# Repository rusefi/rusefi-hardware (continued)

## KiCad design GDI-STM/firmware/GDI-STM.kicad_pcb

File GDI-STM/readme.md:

GDI based on stm32g4

🔴 zero firmware exists for this hardware 🔴

https://github.com/rusefi/rusefi-hardware/issues/306

https://github.com/rusefi/rusefi-hardware/issues/307

https://rusefi.com/forum/viewtopic.php?f=4&t=1337

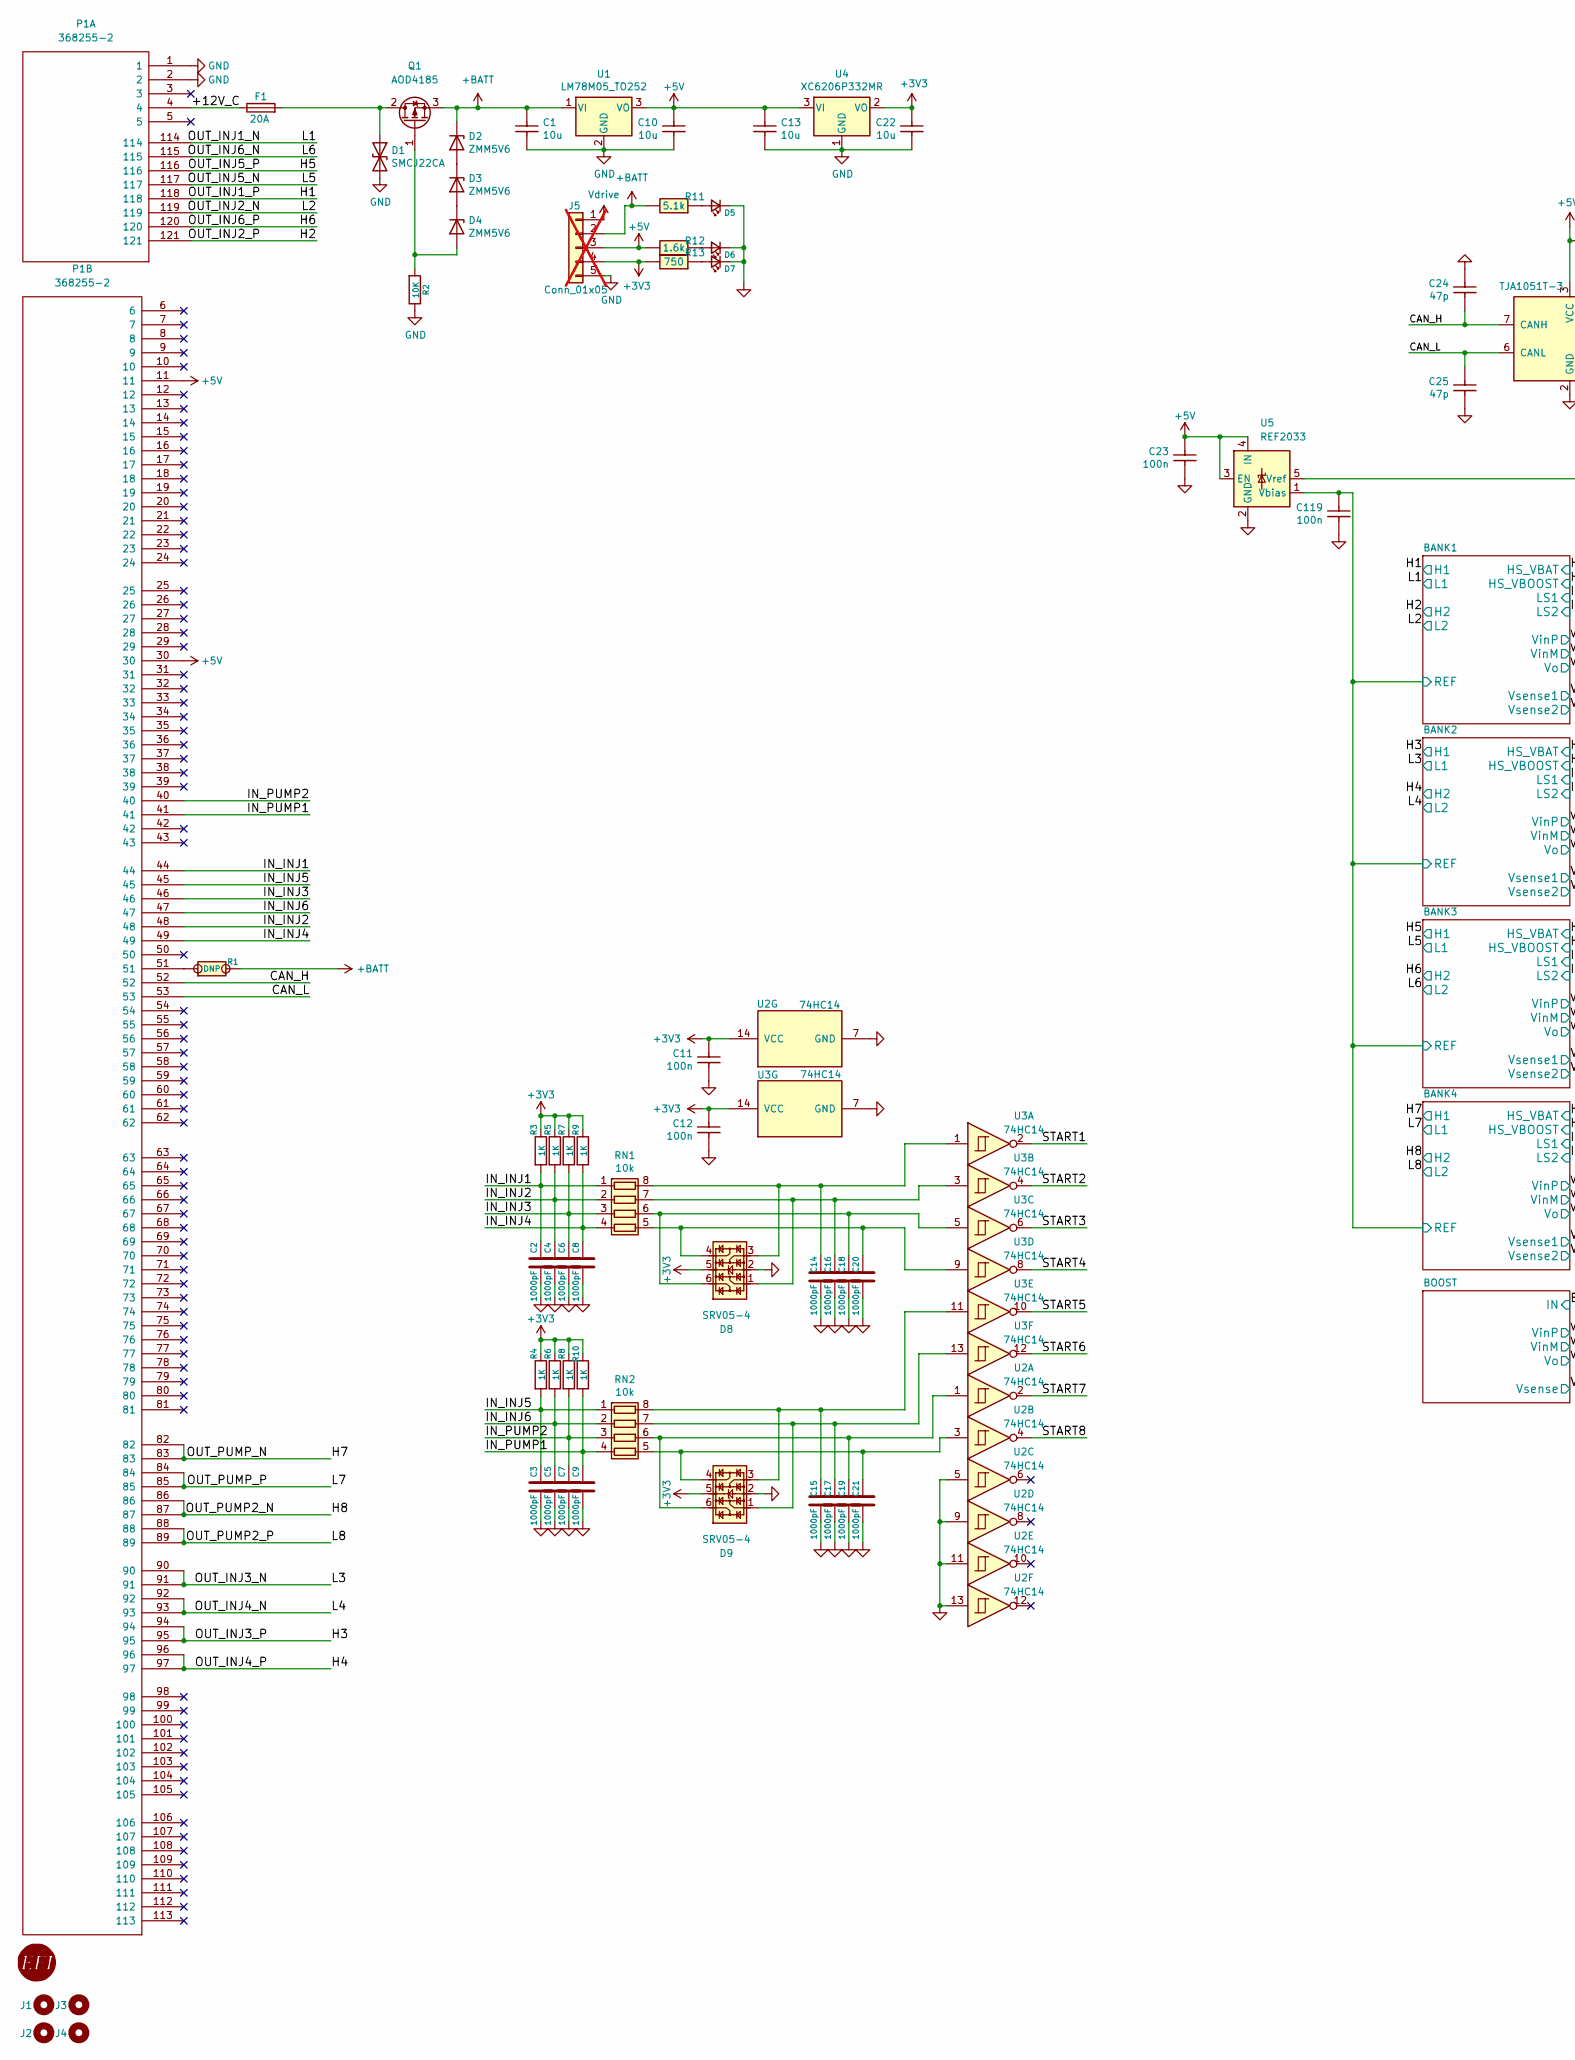
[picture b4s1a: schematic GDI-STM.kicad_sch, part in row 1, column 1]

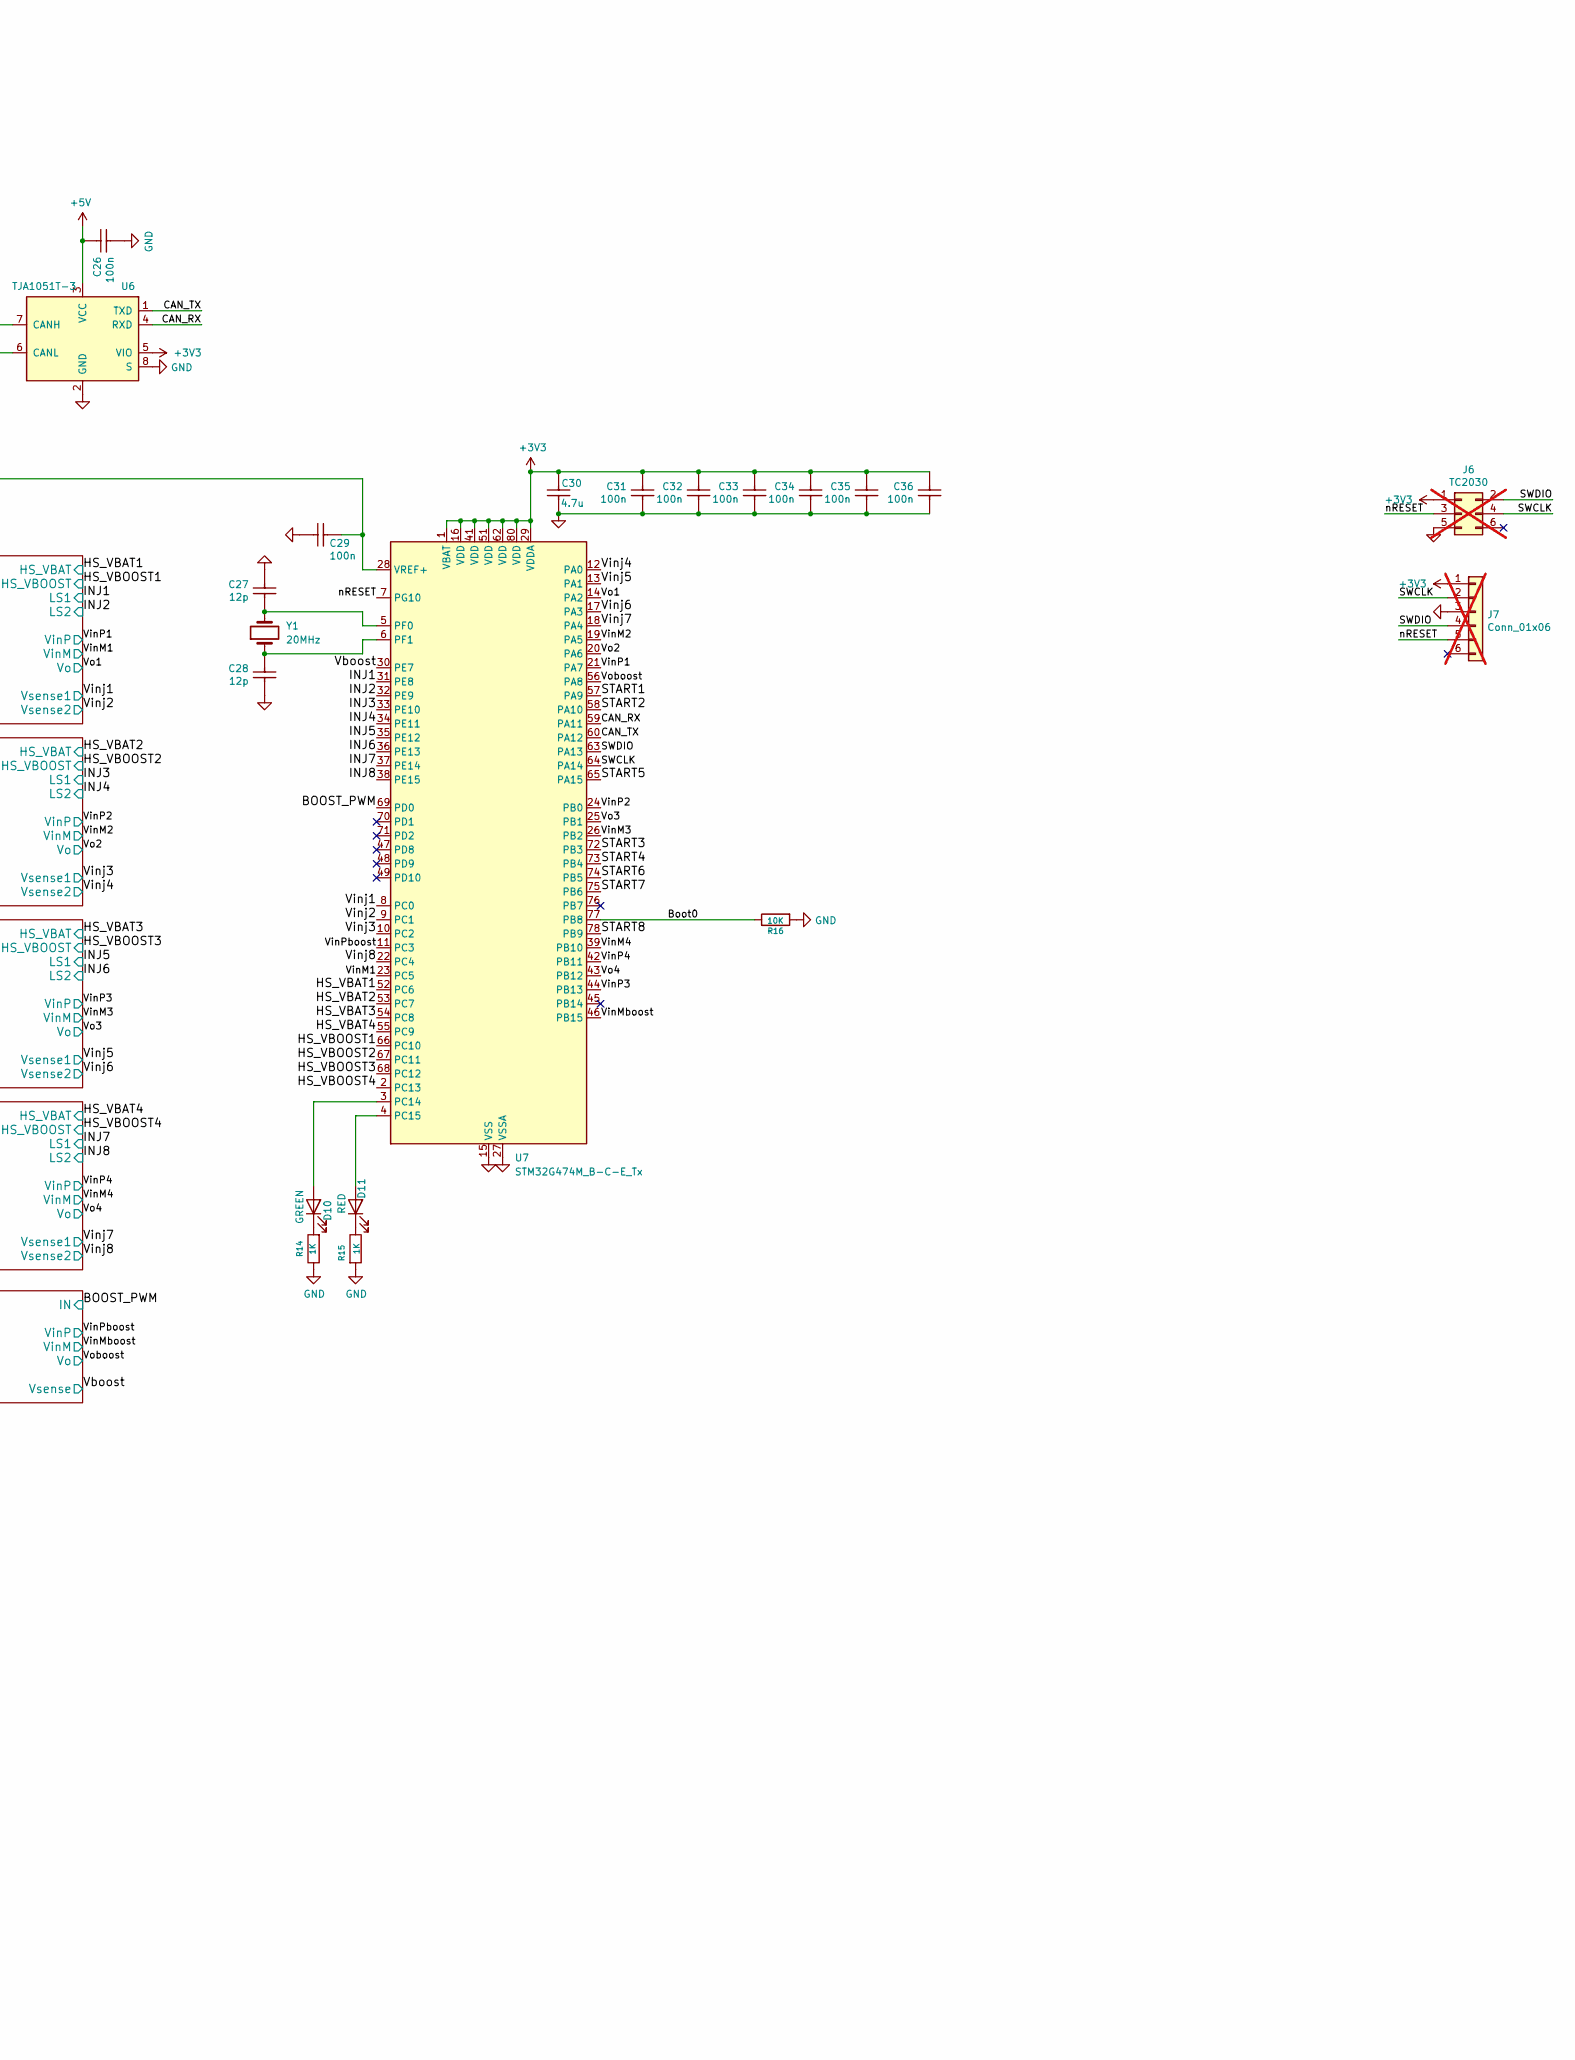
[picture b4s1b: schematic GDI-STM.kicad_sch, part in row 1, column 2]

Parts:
C1, C10, C13, C22: 10u; C_0805_2012Metric; LCSC C15850
C2, C3, C4, C5, C6, C7, C8, C9, C14, C15, C16, C17, C18, C19, C20, C21: 1000pF; C_0603_1608Metric; LCSC C106247
C11, C12, C23, C26, C29, C31, C32, C33, C34, C35, C36, C119: 100n; C0603; LCSC C14663
C24, C25: 47p; C0603; LCSC C1671
C27, C28: 12p; C0603; LCSC C38523
C30: 4.7u; C0603; LCSC C19666
D1: SMCJ22CA; D_SMC; LCSC C151904
D2, D3, D4: ZMM5V6; D_MiniMELF; LCSC C7497481
D5, D6, D7: LED_Small; LED_0805_2012Metric; LCSC C2296
D8, D9: SRV05-4; SOT-23-6; LCSC C85364
D10: GREEN; LED_0603_1608Metric; LCSC C12624
D11: RED; LED_0603_1608Metric; LCSC C2286
F1: 20A; Fuse_1206_3216Metric; LCSC C136357
G1: RUSEFI_LOGO; rusefi_logo
J1, J3: Conn_01x01; MountingHole_3.5mm
J2, J4: Conn_01x01; MountingHole_5.5mm
J5: Conn_01x05; PinHeader_1x05_P2.54mm_Vertical; not fitted
J6: TC2030; Tag-Connect_TC2030-IDC-NL_2x03_P1.27mm_Vertical; not fitted
J7: Conn_01x06; PinHeader_1x06_P2.54mm_Vertical; not fitted
P1: 368255-2; TE_368255-2
Q1: AOD4185; TO-252-2; LCSC C400894
R1: DNP; PAD-0805-PAD
R2, R16: 10K; R_0603_1608Metric; Part # RMCF0603JT10K0; LCSC C25804
R3, R4, R5, R6, R7, R8, R9, R10, R14, R15: 1K; R_0603_1608Metric; LCSC C21190
R11: 5.1k; R0603; LCSC C23186
R12: 1.6k; R0603; LCSC C22847
R13: 750; R0603; LCSC C23241
RN1, RN2: 10k; R_Array_Convex_4x0603; Part # YC164-JR-0710KL; LCSC C29718
U1: LM78M05_TO252; TO-252-2; LCSC C58069
U2, U3: 74HC14; TSSOP-14_4.4x5mm_P0.65mm
U4: XC6206P332MR; SOT-23-3; LCSC C5446
U5: REF2033; SOT-23-5; LCSC C440747
U6: TJA1051T-3; SOIC-8_3.9x4.9mm_P1.27mm; LCSC C38695
U7: STM32G474M_B-C-E_Tx; LQFP-80_12x12mm_P0.5mm; LCSC C5270364
Y1: 20MHz; Crystal_SMD_5032-2Pin_5.0x3.2mm; LCSC C112566

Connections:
+3V3: C11.2, C12.2, C22.2, C30.2, C31.2, C32.2, C33.2, C34.2, C35.2, C36.2, D8.5, D9.5, J5.4, J6.1, J7.1, R3.1, R4.1, R5.1, R6.1, R7.1, R8.1, R9.1, R10.1, R13.2, U2.14 (VCC), U3.14 (VCC), U4.2 (VO), U6.5 (VIO), U7.1 (VBAT), U7.16 (VDD), U7.29 (VDDA), U7.41 (VDD), U7.51 (VDD), U7.62 (VDD), U7.80 (VDD); also elsewhere on the board
+5V: C10.2, C13.2, C23.2, C26.2, J5.3, P1.11, P1.30, R12.2, U1.3 (VO), U4.3 (VI), U5.3 (EN), U5.4 (IN), U6.3 (VCC)
+BATT: C1.2, D2.1 (K), J5.2, Q1.3 (S), R1.2, R11.2, U1.1 (VI); also elsewhere on the board
/+12V_C: F1.1, P1.4
/BANK1/REF: C119.2, U5.1 (Vbias); also elsewhere on the board
/BOOST_PWM: U7.69 (PD0); also elsewhere on the board
/Boot0: R16.1, U7.77 (PB8)
/CAN_H: C24.1, P1.52, U6.7 (CANH)
/CAN_L: C25.2, P1.53, U6.6 (CANL)
/CAN_RX: U6.4 (RXD), U7.59 (PA11)
/CAN_TX: U6.1 (TXD), U7.60 (PA12)
/H1: P1.118, P1.121; also elsewhere on the board
/H3: P1.94, P1.95, P1.96, P1.97; also elsewhere on the board
/H5: P1.116, P1.120; also elsewhere on the board
/H7: P1.82, P1.83, P1.86, P1.87; also elsewhere on the board
/HS_VBAT1: U7.52 (PC6); also elsewhere on the board
/HS_VBAT2: U7.53 (PC7); also elsewhere on the board
/HS_VBAT3: U7.54 (PC8); also elsewhere on the board
/HS_VBAT4: U7.55 (PC9); also elsewhere on the board
/HS_VBOOST1: U7.66 (PC10); also elsewhere on the board
/HS_VBOOST2: U7.67 (PC11); also elsewhere on the board
/HS_VBOOST3: U7.68 (PC12); also elsewhere on the board
/HS_VBOOST4: U7.2 (PC13); also elsewhere on the board
/INJ1: U7.31 (PE8); also elsewhere on the board
/INJ2: U7.32 (PE9); also elsewhere on the board
/INJ3: U7.33 (PE10); also elsewhere on the board
/INJ4: U7.34 (PE11); also elsewhere on the board
/INJ5: U7.35 (PE12); also elsewhere on the board
/INJ6: U7.36 (PE13); also elsewhere on the board
/INJ7: U7.37 (PE14); also elsewhere on the board
/INJ8: U7.38 (PE15); also elsewhere on the board
/IN_INJ1: C2.2, P1.44, R3.2, RN1.1 (R1.1)
/IN_INJ2: C4.2, P1.48, R5.2, RN1.2 (R2.1)
/IN_INJ3: C6.2, P1.46, R7.2, RN1.3 (R3.1)
/IN_INJ4: C8.2, P1.49, R9.2, RN1.4 (R4.1)
/IN_INJ5: C3.2, P1.45, R4.2, RN2.1 (R1.1)
/IN_INJ6: C5.2, P1.47, R6.2, RN2.2 (R2.1)
/IN_PUMP1: C9.2, P1.41, R10.2, RN2.4 (R4.1)
/IN_PUMP2: C7.2, P1.40, R8.2, RN2.3 (R3.1)
/L1: P1.114; also elsewhere on the board
/L2: P1.119; also elsewhere on the board
/L3: P1.90, P1.91; also elsewhere on the board
/L4: P1.92, P1.93; also elsewhere on the board
/L5: P1.117; also elsewhere on the board
/L6: P1.115; also elsewhere on the board
/L7: P1.84, P1.85; also elsewhere on the board
/L8: P1.88, P1.89; also elsewhere on the board
/START1: U3.2, U7.57 (PA9)
/START2: U3.4, U7.58 (PA10)
/START3: U3.6, U7.72 (PB3)
/START4: U3.8, U7.73 (PB4)
/START5: U3.10, U7.65 (PA15)
/START6: U3.12, U7.74 (PB5)
/START7: U2.2, U7.75 (PB6)
/START8: U2.4, U7.78 (PB9)
/SWCLK: J6.4, J7.2, U7.64 (PA14)
/SWDIO: J6.2, J7.4, U7.63 (PA13)
/Vboost: U7.30 (PE7); also elsewhere on the board
/VinM1: U7.23 (PC5); also elsewhere on the board
/VinM2: U7.19 (PA5); also elsewhere on the board
/VinM3: U7.26 (PB2); also elsewhere on the board
/VinM4: U7.39 (PB10); also elsewhere on the board
/VinMboost: U7.46 (PB15); also elsewhere on the board
/VinP1: U7.21 (PA7); also elsewhere on the board
/VinP2: U7.24 (PB0); also elsewhere on the board
/VinP3: U7.44 (PB13); also elsewhere on the board
/VinP4: U7.42 (PB11); also elsewhere on the board
/VinPboost: U7.11 (PC3); also elsewhere on the board
/Vinj1: U7.8 (PC0); also elsewhere on the board
/Vinj2: U7.9 (PC1); also elsewhere on the board
/Vinj3: U7.10 (PC2); also elsewhere on the board
/Vinj4: U7.12 (PA0); also elsewhere on the board
/Vinj5: U7.13 (PA1); also elsewhere on the board
/Vinj6: U7.17 (PA3); also elsewhere on the board
/Vinj7: U7.18 (PA4); also elsewhere on the board
/Vinj8: U7.22 (PC4); also elsewhere on the board
/Vo1: U7.14 (PA2); also elsewhere on the board
/Vo2: U7.20 (PA6); also elsewhere on the board
/Vo3: U7.25 (PB1); also elsewhere on the board
/Vo4: U7.43 (PB12); also elsewhere on the board
/Voboost: U7.56 (PA8); also elsewhere on the board
/nRESET: J6.3, J7.5, U7.7 (PG10)
GND: C1.1, C2.1, C3.1, C4.1, C5.1, C6.1, C7.1, C8.1, C9.1, C10.1, C11.1, C12.1, C13.1, C14.1, C15.1, C16.1, C17.1, C18.1, C19.1, C20.1, C21.1, C22.1, C23.1, C24.2, C25.1, C26.1, C27.2, C28.1, C29.1, C30.1, C31.1, C32.1, C33.1, C34.1, C35.1, C36.1, C119.1, D1.2 (A2), D5.1 (K), D6.1 (K), D7.1 (K), D8.2, D9.2, J5.5, J6.5, J7.3, P1.1, P1.2, R2.1, R14.1, R15.2, R16.2, U1.2 (GND), U2.5, U2.7 (GND), U2.9, U2.11, U2.13, U3.7 (GND), U4.1 (GND), U5.2 (GND), U6.2 (GND), U6.8 (S), U7.15 (VSS), U7.27 (VSSA), U7.40 (VSS), U7.50 (VSS), U7.61 (VSS), U7.79 (VSS); also elsewhere on the board
unnamed: D1.1 (A1), F1.2, Q1.2 (D)
unnamed: D2.2 (A), D3.1 (K)
unnamed: D3.2 (A), D4.1 (K)
unnamed: D4.2 (A), Q1.1 (G), R2.2
unnamed: D5.2 (A), R11.1
unnamed: D6.2 (A), R12.1
unnamed: D7.2 (A), R13.1
unnamed: D10.2 (A), U7.3 (PC14)
unnamed: D10.1 (K), R14.2
unnamed: D11.2 (A), U7.4 (PC15)
unnamed: D11.1 (K), R15.1
unnamed: P1.51, R1.1
unnamed: C14.2, D8.3, RN1.8 (R1.2), U3.1
unnamed: C16.2, D8.1, RN1.7 (R2.2), U3.3
unnamed: C18.2, D8.6, RN1.6 (R3.2), U3.5
unnamed: C20.2, D8.4, RN1.5 (R4.2), U3.9
unnamed: C15.2, D9.3, RN2.8 (R1.2), U3.11
unnamed: C17.2, D9.1, RN2.7 (R2.2), U3.13
unnamed: C19.2, D9.6, RN2.6 (R3.2), U2.1
unnamed: C21.2, D9.4, RN2.5 (R4.2), U2.3
unnamed: C29.2, U5.5 (Vref), U7.28 (VREF+)
unnamed: C27.1, U7.5 (PF0), Y1.2
unnamed: C28.2, U7.6 (PF1), Y1.1
Vdrive: J5.1; also elsewhere on the board

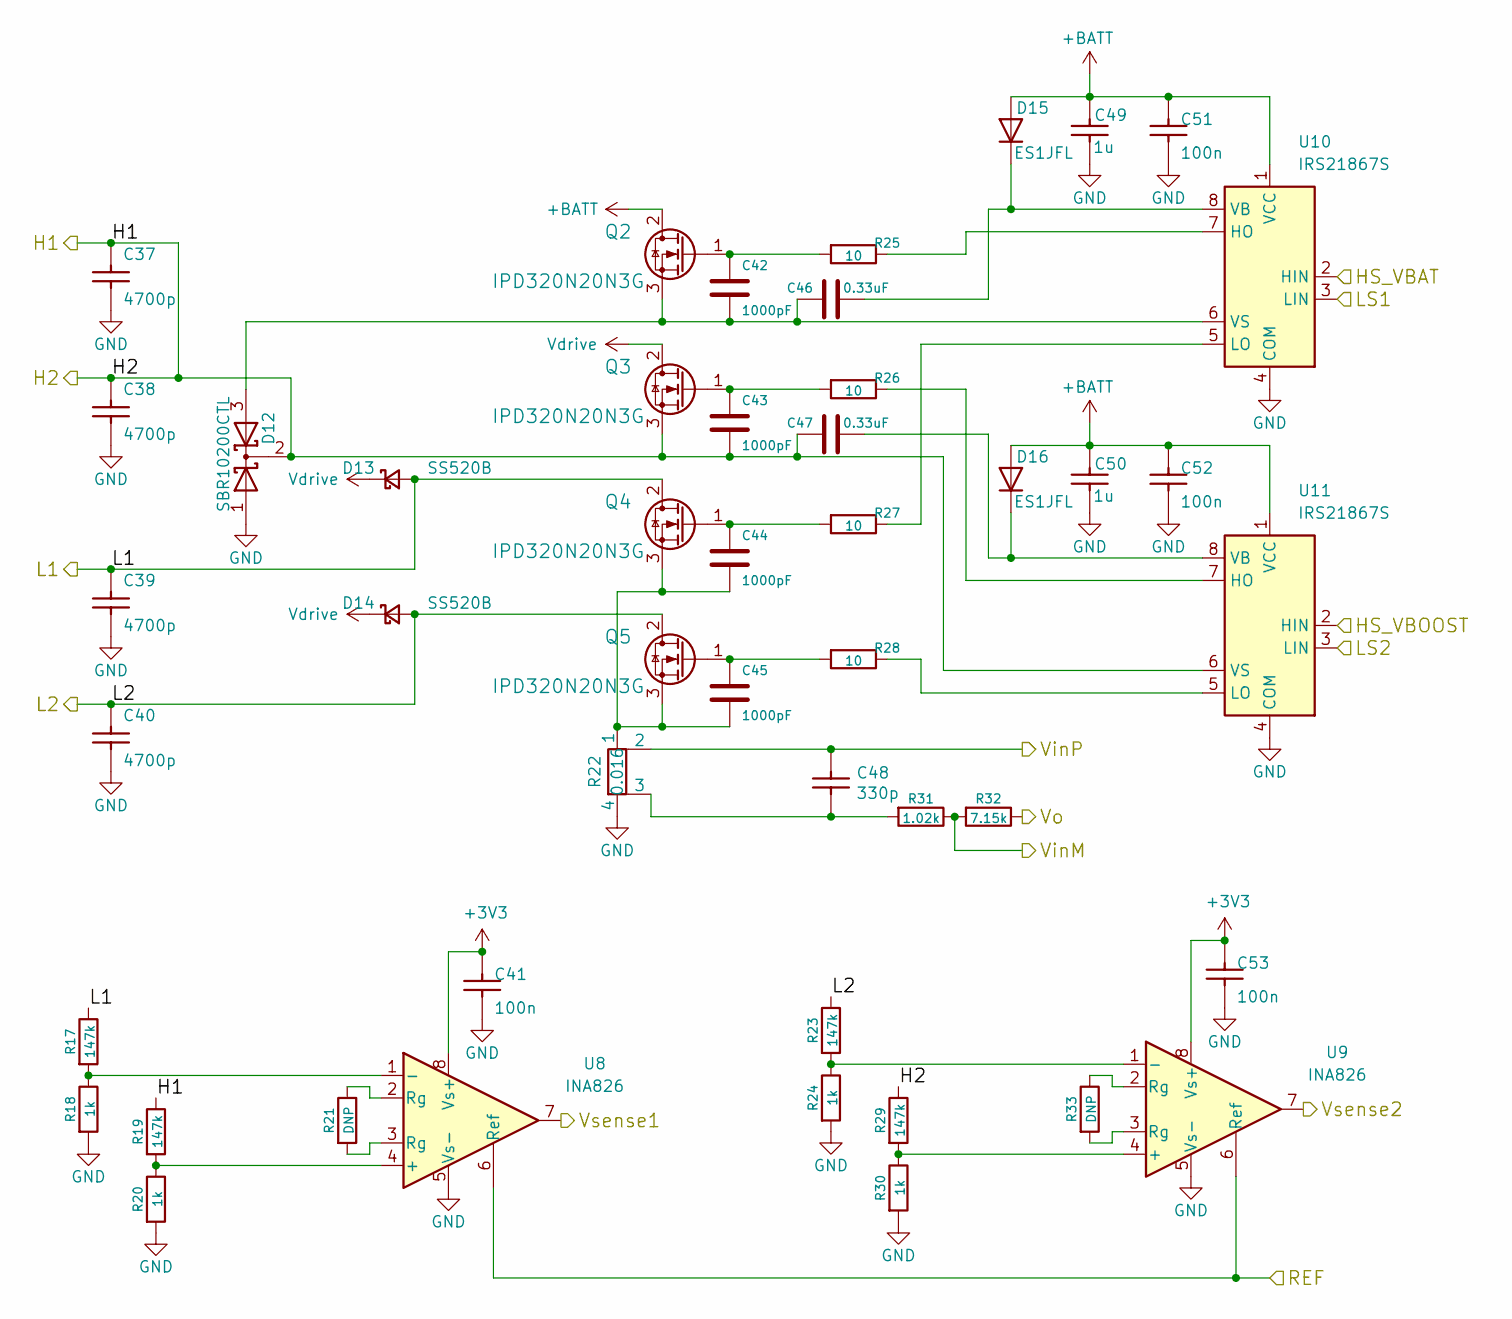
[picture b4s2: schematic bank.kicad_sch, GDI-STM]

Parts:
C37, C38, C39, C40: 4700p; C0603; LCSC C327158
C41, C51, C52, C53: 100n; C0603; LCSC C14663
C42, C43, C44, C45: 1000pF; C_0603_1608Metric; LCSC C106247
C46, C47: 0.33uF; C_0603_1608Metric; LCSC C1615
C48: 330p; C0603; LCSC C576850
C49, C50: 1u; C0603; LCSC C15849
D12: SBR10200CTL; TO-252-2; LCSC C459529
D13, D14: SS520B; D_SMB; LCSC C382826
D15, D16: ES1JFL; D_SOD-123F; LCSC C719809
Q2, Q3, Q4, Q5: IPD320N20N3G; TO-252-2; LCSC C501515
R17, R19, R23, R29: 147k; R_0603_1608Metric; LCSC C22878
R18, R20, R24, R30: 1k; R_0603_1608Metric; LCSC C21190
R21, R33: DNP; R_0603_1608Metric
R22: 0.016; R_Shunt_Vishay_WSK2512_6332Metric_T1.19mm; LCSC C915978
R25, R26, R27, R28: 10; R_0603_1608Metric; LCSC C22859
R31: 1.02k; R_0603_1608Metric; LCSC C22831
R32: 7.15k; R_0603_1608Metric; LCSC C25980
U8, U9: INA826; SOIC-8_3.9x4.9mm_P1.27mm; LCSC C38433
U10, U11: IRS21867S; SOIC-8_3.9x4.9mm_P1.27mm; LCSC C52290

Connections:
+3V3: C41.2, C53.2, U8.8 (Vs+), U9.8 (Vs+); also elsewhere on the board
+BATT: C49.2, C50.2, C51.2, C52.2, D15.2 (A), D16.2 (A), Q2.2 (D), U10.1 (VCC), U11.1 (VCC); also elsewhere on the board
/BANK1/REF: U8.6 (Ref), U9.6 (Ref); also elsewhere on the board
/H1: C37.2, C38.2, C43.1, C47.2, D12.2 (K), Q3.3 (S), R19.1, R29.1, U11.6 (VS); also elsewhere on the board
/HS_VBAT1: U10.2 (HIN); also elsewhere on the board
/HS_VBOOST1: U11.2 (HIN); also elsewhere on the board
/INJ1: U10.3 (LIN); also elsewhere on the board
/INJ2: U11.3 (LIN); also elsewhere on the board
/L1: C39.2, D13.2 (A), Q4.2 (D), R17.1; also elsewhere on the board
/L2: C40.2, D14.2 (A), Q5.2 (D), R23.1; also elsewhere on the board
/VinM1: R31.1, R32.2; also elsewhere on the board
/VinP1: C48.2, R22.2; also elsewhere on the board
/Vinj1: U8.7; also elsewhere on the board
/Vinj2: U9.7; also elsewhere on the board
/Vo1: R32.1; also elsewhere on the board
GND: C37.1, C38.1, C39.1, C40.1, C41.1, C49.1, C50.1, C51.1, C52.1, C53.1, D12.1 (A), R18.2, R20.2, R22.4, R24.2, R30.2, U8.5 (Vs-), U9.5 (Vs-), U10.4 (COM), U11.4 (COM); also elsewhere on the board
unnamed: C48.1, R22.3, R31.2
unnamed: C46.1, D15.1 (K), U10.8 (VB)
unnamed: C47.1, D16.1 (K), U11.8 (VB)
unnamed: C42.2, Q2.1 (G), R25.2
unnamed: C42.1, C46.2, D12.3 (A), Q2.3 (S), U10.6 (VS)
unnamed: C43.2, Q3.1 (G), R26.2
unnamed: C44.2, Q4.1 (G), R27.2
unnamed: C44.1, C45.1, Q4.3 (S), Q5.3 (S), R22.1
unnamed: C45.2, Q5.1 (G), R28.2
unnamed: R21.1, U8.2 (Rg)
unnamed: R21.2, U8.3 (Rg)
unnamed: R33.1, U9.2 (Rg)
unnamed: R33.2, U9.3 (Rg)
unnamed: R19.2, R20.1, U8.4 (+)
unnamed: R17.2, R18.1, U8.1 (-)
unnamed: R29.2, R30.1, U9.4 (+)
unnamed: R23.2, R24.1, U9.1 (-)
unnamed: R25.1, U10.7 (HO)
unnamed: R27.1, U10.5 (LO)
unnamed: R26.1, U11.7 (HO)
unnamed: R28.1, U11.5 (LO)
Vdrive: D13.1 (K), D14.1 (K), Q3.2 (D); also elsewhere on the board

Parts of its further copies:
C54, C55, C56, C57, C71, C72, C73, C74, C88, C89, C90, C91: 4700p; C0603; LCSC C327158
C58, C68, C69, C70, C75, C85, C86, C87, C92, C102, C103, C104: 100n; C0603; LCSC C14663
C59, C60, C61, C62, C76, C77, C78, C79, C93, C94, C95, C96: 1000pF; C_0603_1608Metric; LCSC C106247
C63, C64, C80, C81, C97, C98: 0.33uF; C_0603_1608Metric; LCSC C1615
C65, C82, C99: 330p; C0603; LCSC C576850
C66, C67, C83, C84, C100, C101: 1u; C0603; LCSC C15849
D17, D22, D27: SBR10200CTL; TO-252-2; LCSC C459529
D18, D19, D23, D24, D28, D29: SS520B; D_SMB; LCSC C382826
D20, D21, D25, D26, D30, D31: ES1JFL; D_SOD-123F; LCSC C719809
Q6, Q7, Q8, Q9, Q10, Q11, Q12, Q13, Q14, Q15, Q16, Q17: IPD320N20N3G; TO-252-2; LCSC C501515
R34, R36, R40, R46, R51, R53, R57, R63, R68, R70, R74, R80: 147k; R_0603_1608Metric; LCSC C22878
R35, R37, R41, R47, R52, R54, R58, R64, R69, R71, R75, R81: 1k; R_0603_1608Metric; LCSC C21190
R38, R50, R55, R67, R72, R84: DNP; R_0603_1608Metric
R39, R56, R73: 0.016; R_Shunt_Vishay_WSK2512_6332Metric_T1.19mm; LCSC C915978
R42, R43, R44, R45, R59, R60, R61, R62, R76, R77, R78, R79: 10; R_0603_1608Metric; LCSC C22859
R48, R65, R82: 1.02k; R_0603_1608Metric; LCSC C22831
R49, R66, R83: 7.15k; R_0603_1608Metric; LCSC C25980
U12, U13, U16, U17, U20, U21: INA826; SOIC-8_3.9x4.9mm_P1.27mm; LCSC C38433
U14, U15, U18, U19, U22, U23: IRS21867S; SOIC-8_3.9x4.9mm_P1.27mm; LCSC C52290

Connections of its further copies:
+3V3: C58.2, C70.2, C75.2, C87.2, C92.2, C104.2, U12.8 (Vs+), U13.8 (Vs+), U16.8 (Vs+), U17.8 (Vs+), U20.8 (Vs+), U21.8 (Vs+); also elsewhere on the board
+BATT: C66.2, C67.2, C68.2, C69.2, C83.2, C84.2, C85.2, C86.2, C100.2, C101.2, C102.2, C103.2, D20.2 (A), D21.2 (A), D25.2 (A), D26.2 (A), D30.2 (A), D31.2 (A), Q6.2 (D), Q10.2 (D), Q14.2 (D), U14.1 (VCC), U15.1 (VCC), U18.1 (VCC), U19.1 (VCC), U22.1 (VCC), U23.1 (VCC); also elsewhere on the board
/BANK1/REF: U12.6 (Ref), U13.6 (Ref), U16.6 (Ref), U17.6 (Ref), U20.6 (Ref), U21.6 (Ref); also elsewhere on the board
/H3: C54.2, C55.2, C60.1, C64.2, D17.2 (K), Q7.3 (S), R36.1, R46.1, U15.6 (VS); also elsewhere on the board
/H5: C71.2, C72.2, C77.1, C81.2, D22.2 (K), Q11.3 (S), R53.1, R63.1, U19.6 (VS); also elsewhere on the board
/H7: C88.2, C89.2, C94.1, C98.2, D27.2 (K), Q15.3 (S), R70.1, R80.1, U23.6 (VS); also elsewhere on the board
/HS_VBAT2: U14.2 (HIN); also elsewhere on the board
/HS_VBAT3: U18.2 (HIN); also elsewhere on the board
/HS_VBAT4: U22.2 (HIN); also elsewhere on the board
/HS_VBOOST2: U15.2 (HIN); also elsewhere on the board
/HS_VBOOST3: U19.2 (HIN); also elsewhere on the board
/HS_VBOOST4: U23.2 (HIN); also elsewhere on the board
/INJ3: U14.3 (LIN); also elsewhere on the board
/INJ4: U15.3 (LIN); also elsewhere on the board
/INJ5: U18.3 (LIN); also elsewhere on the board
/INJ6: U19.3 (LIN); also elsewhere on the board
/INJ7: U22.3 (LIN); also elsewhere on the board
/INJ8: U23.3 (LIN); also elsewhere on the board
/L3: C56.2, D18.2 (A), Q8.2 (D), R34.1; also elsewhere on the board
/L4: C57.2, D19.2 (A), Q9.2 (D), R40.1; also elsewhere on the board
/L5: C73.2, D23.2 (A), Q12.2 (D), R51.1; also elsewhere on the board
/L6: C74.2, D24.2 (A), Q13.2 (D), R57.1; also elsewhere on the board
/L7: C90.2, D28.2 (A), Q16.2 (D), R68.1; also elsewhere on the board
/L8: C91.2, D29.2 (A), Q17.2 (D), R74.1; also elsewhere on the board
/VinM2: R48.1, R49.2; also elsewhere on the board
/VinM3: R65.1, R66.2; also elsewhere on the board
/VinM4: R82.1, R83.2; also elsewhere on the board
/VinP2: C65.2, R39.2; also elsewhere on the board
/VinP3: C82.2, R56.2; also elsewhere on the board
/VinP4: C99.2, R73.2; also elsewhere on the board
/Vinj3: U12.7; also elsewhere on the board
/Vinj4: U13.7; also elsewhere on the board
/Vinj5: U16.7; also elsewhere on the board
/Vinj6: U17.7; also elsewhere on the board
/Vinj7: U20.7; also elsewhere on the board
/Vinj8: U21.7; also elsewhere on the board
/Vo2: R49.1; also elsewhere on the board
/Vo3: R66.1; also elsewhere on the board
/Vo4: R83.1; also elsewhere on the board
GND: C54.1, C55.1, C56.1, C57.1, C58.1, C66.1, C67.1, C68.1, C69.1, C70.1, C71.1, C72.1, C73.1, C74.1, C75.1, C83.1, C84.1, C85.1, C86.1, C87.1, C88.1, C89.1, C90.1, C91.1, C92.1, C100.1, C101.1, C102.1, C103.1, C104.1, D17.1 (A), D22.1 (A), D27.1 (A), R35.2, R37.2, R39.4, R41.2, R47.2, R52.2, R54.2, R56.4, R58.2, R64.2, R69.2, R71.2, R73.4, R75.2, R81.2, U12.5 (Vs-), U13.5 (Vs-), U14.4 (COM), U15.4 (COM), U16.5 (Vs-), U17.5 (Vs-), U18.4 (COM), U19.4 (COM), U20.5 (Vs-), U21.5 (Vs-), U22.4 (COM), U23.4 (COM); also elsewhere on the board
unnamed: C65.1, R39.3, R48.2
unnamed: C82.1, R56.3, R65.2
unnamed: C99.1, R73.3, R82.2
unnamed: C63.1, D20.1 (K), U14.8 (VB)
unnamed: C64.1, D21.1 (K), U15.8 (VB)
unnamed: C80.1, D25.1 (K), U18.8 (VB)
unnamed: C81.1, D26.1 (K), U19.8 (VB)
unnamed: C97.1, D30.1 (K), U22.8 (VB)
unnamed: C98.1, D31.1 (K), U23.8 (VB)
unnamed: C59.2, Q6.1 (G), R42.2
unnamed: C59.1, C63.2, D17.3 (A), Q6.3 (S), U14.6 (VS)
unnamed: C60.2, Q7.1 (G), R43.2
unnamed: C61.2, Q8.1 (G), R44.2
unnamed: C61.1, C62.1, Q8.3 (S), Q9.3 (S), R39.1
unnamed: C62.2, Q9.1 (G), R45.2
unnamed: C76.2, Q10.1 (G), R59.2
unnamed: C76.1, C80.2, D22.3 (A), Q10.3 (S), U18.6 (VS)
unnamed: C77.2, Q11.1 (G), R60.2
unnamed: C78.2, Q12.1 (G), R61.2
unnamed: C78.1, C79.1, Q12.3 (S), Q13.3 (S), R56.1
unnamed: C79.2, Q13.1 (G), R62.2
unnamed: C93.2, Q14.1 (G), R76.2
unnamed: C93.1, C97.2, D27.3 (A), Q14.3 (S), U22.6 (VS)
unnamed: C94.2, Q15.1 (G), R77.2
unnamed: C95.2, Q16.1 (G), R78.2
unnamed: C95.1, C96.1, Q16.3 (S), Q17.3 (S), R73.1
unnamed: C96.2, Q17.1 (G), R79.2
unnamed: R38.1, U12.2 (Rg)
unnamed: R38.2, U12.3 (Rg)
unnamed: R50.1, U13.2 (Rg)
unnamed: R50.2, U13.3 (Rg)
unnamed: R55.1, U16.2 (Rg)
unnamed: R55.2, U16.3 (Rg)
unnamed: R67.1, U17.2 (Rg)
unnamed: R67.2, U17.3 (Rg)
unnamed: R72.1, U20.2 (Rg)
unnamed: R72.2, U20.3 (Rg)
unnamed: R84.1, U21.2 (Rg)
unnamed: R84.2, U21.3 (Rg)
unnamed: R36.2, R37.1, U12.4 (+)
unnamed: R34.2, R35.1, U12.1 (-)
unnamed: R46.2, R47.1, U13.4 (+)
unnamed: R40.2, R41.1, U13.1 (-)
unnamed: R42.1, U14.7 (HO)
unnamed: R44.1, U14.5 (LO)
unnamed: R43.1, U15.7 (HO)
unnamed: R45.1, U15.5 (LO)
unnamed: R53.2, R54.1, U16.4 (+)
unnamed: R51.2, R52.1, U16.1 (-)
unnamed: R63.2, R64.1, U17.4 (+)
unnamed: R57.2, R58.1, U17.1 (-)
unnamed: R59.1, U18.7 (HO)
unnamed: R61.1, U18.5 (LO)
unnamed: R60.1, U19.7 (HO)
unnamed: R62.1, U19.5 (LO)
unnamed: R70.2, R71.1, U20.4 (+)
unnamed: R68.2, R69.1, U20.1 (-)
unnamed: R80.2, R81.1, U21.4 (+)
unnamed: R74.2, R75.1, U21.1 (-)
unnamed: R76.1, U22.7 (HO)
unnamed: R78.1, U22.5 (LO)
unnamed: R77.1, U23.7 (HO)
unnamed: R79.1, U23.5 (LO)
Vdrive: D18.1 (K), D19.1 (K), D23.1 (K), D24.1 (K), D28.1 (K), D29.1 (K), Q7.2 (D), Q11.2 (D), Q15.2 (D); also elsewhere on the board

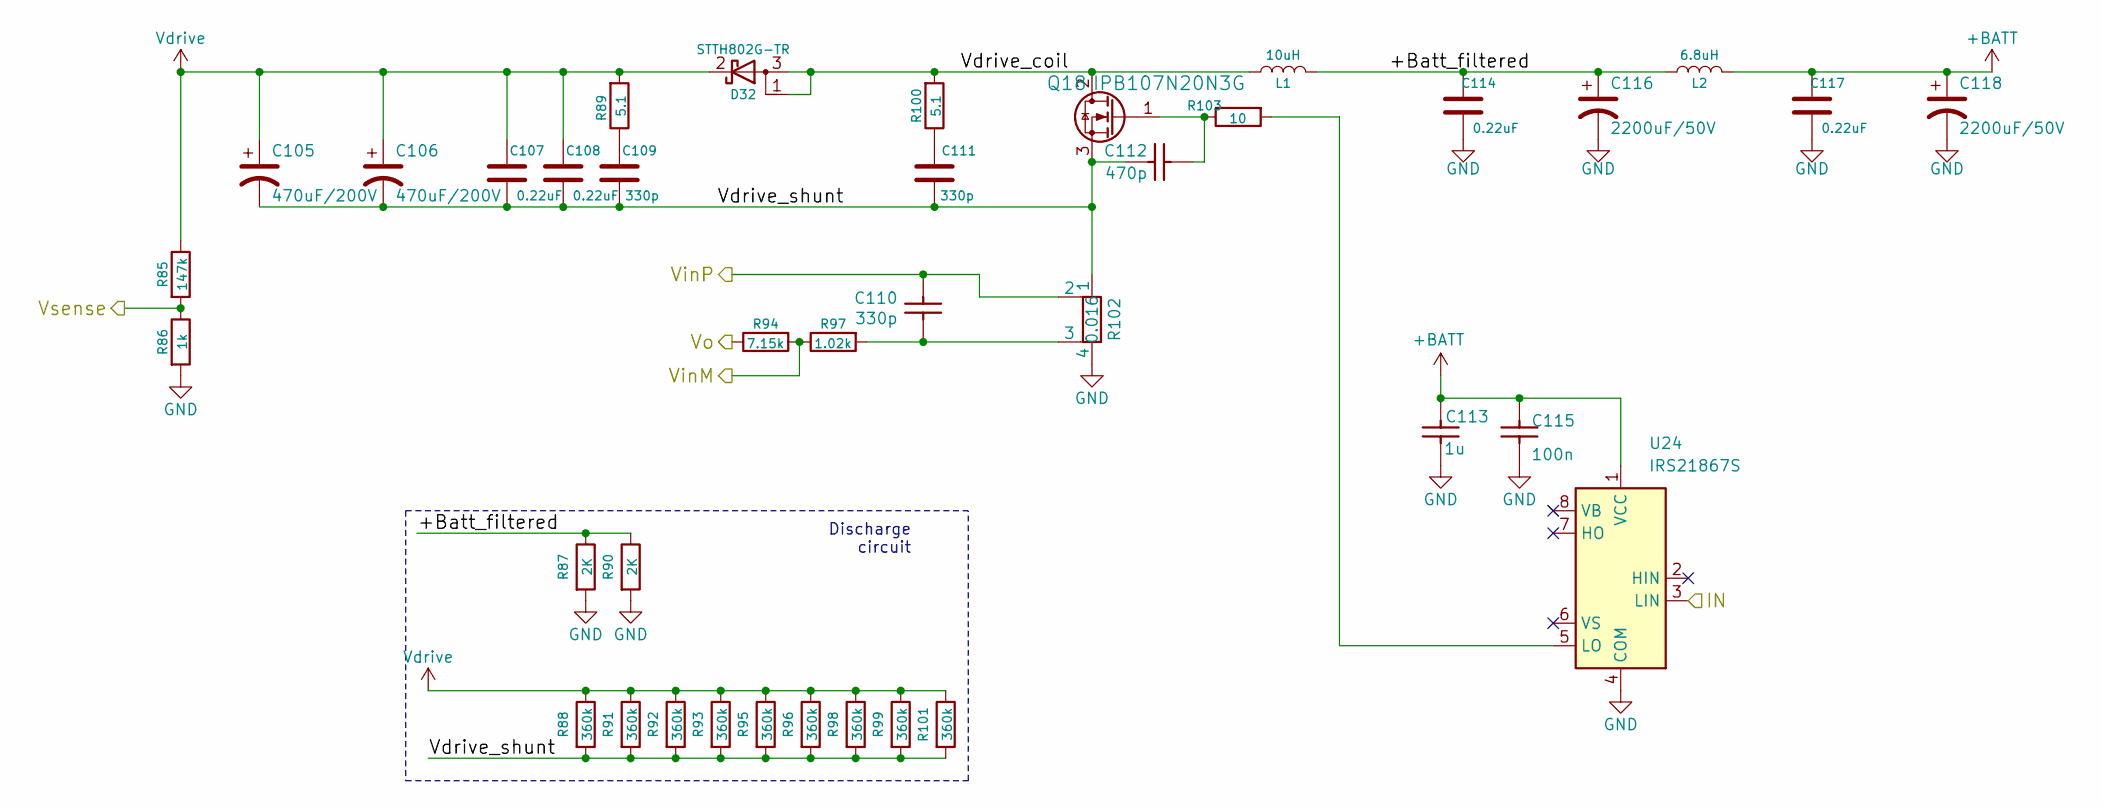
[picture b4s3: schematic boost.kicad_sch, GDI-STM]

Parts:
C105, C106: 470uF/200V; CP_Radial_D18.0mm_P7.50mm; LCSC C160144
C107, C108, C114, C117: 0.22uF; C_1206_3216Metric; LCSC C106048
C109, C111: 330p; C_0805_2012Metric; LCSC C113837
C110: 330p; C0603; LCSC C576850
C112: 470p; C0603; LCSC C326973
C113: 1u; C0603; LCSC C15849
C115: 100n; C0603; LCSC C14663
C116, C118: 2200uF/50V; CP_Radial_D18.0mm_P7.50mm; LCSC C106661
D32: STTH802G-TR; TO-263-2; LCSC C181034
L1: 10uH; L_Changjiang_FXL2213; LCSC C22378757
L2: 6.8uH; L_Changjiang_FXL1360; LCSC C7471128
Q18: IPB107N20N3G; TO-263-2; LCSC C444895
R85: 147k; R_0603_1608Metric; LCSC C22878
R86: 1k; R_0603_1608Metric; LCSC C21190
R87, R90: 2K; R_1206_3216Metric; LCSC C17944
R88, R91, R92, R93, R95, R96, R98, R99, R101: 360k; R_0805_2012Metric; LCSC C17645
R89, R100: 5.1; R_0603_1608Metric; LCSC C25197
R94: 7.15k; R_0603_1608Metric; LCSC C25980
R97: 1.02k; R_0603_1608Metric; LCSC C22831
R102: 0.016; R_Shunt_Vishay_WSK2512_6332Metric_T1.19mm; LCSC C915978
R103: 10; R_0603_1608Metric; LCSC C22859
U24: IRS21867S; SOIC-8_3.9x4.9mm_P1.27mm; LCSC C52290

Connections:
+BATT: C113.2, C115.2, C117.1, C118.1, L2.1, U24.1 (VCC); also elsewhere on the board
/BOOST/+Batt_filtered: C114.1, C116.1, L1.1, L2.2, R87.1, R90.1
/BOOST/Vdrive_coil: D32.1 (A), D32.3 (A), L1.2, Q18.2 (D), R100.2
/BOOST/Vdrive_shunt: C105.2, C106.2, C107.2, C108.2, C109.2, C111.2, C112.1, Q18.3 (S), R88.2, R91.2, R92.2, R93.2, R95.2, R96.2, R98.2, R99.2, R101.2, R102.1
/BOOST_PWM: U24.3 (LIN); also elsewhere on the board
/Vboost: R85.2, R86.1; also elsewhere on the board
/VinMboost: R94.2, R97.1; also elsewhere on the board
/VinPboost: C110.2, R102.2; also elsewhere on the board
/Voboost: R94.1; also elsewhere on the board
GND: C113.1, C114.2, C115.1, C116.2, C117.2, C118.2, R86.2, R87.2, R90.2, R102.4, U24.4 (COM); also elsewhere on the board
unnamed: C109.1, R89.1
unnamed: C110.1, R97.2, R102.3
unnamed: C111.1, R100.1
unnamed: C112.2, Q18.1 (G), R103.1
unnamed: R103.2, U24.5 (LO)
Vdrive: C105.1, C106.1, C107.1, C108.1, D32.2 (K), R85.1, R88.1, R89.2, R91.1, R92.1, R93.1, R95.1, R96.1, R98.1, R99.1, R101.1; also elsewhere on the board

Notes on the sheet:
Discharge circuit
